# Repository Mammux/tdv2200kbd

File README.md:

# tdv2200kbd

Using the keyboard from a Tandberg **TDV 2200 S** terminal (sold by Norsk Data
as the **ND 320**, item no. 4580) as a USB keyboard on a modern computer.

<p align="center">
  
  <br>
  <sub>A TDV 2200/9S terminal sold as the ND 246 (1984), with the same family of
  NOTIS keyboard. Photo: Torfinn Ingolfsen,
  <a href="https://creativecommons.org/licenses/by-sa/3.0/">CC BY-SA 3.0</a>,
  via <a href="https://deskthority.net/wiki/File:ND246-Notis-TDV2200-9S-1984.jpg">Deskthority</a>.</sub>
</p>

The keyboard has its own 8035 microcontroller and talks to the terminal over
an RS-422 serial link. This project has two parts:

1. **An adapter**: a Raspberry Pi Pico (RP2040) and a MAX3490 RS-422
   transceiver between the keyboard's DE-9 plug and USB.
2. **New keyboard firmware**: the original firmware only sends a character
   when a key is pressed, with Shift and Ctrl applied inside the keyboard.
   A USB keyboard needs separate press and release events for every key,
   including the modifiers, so the 2716 EPROM is replaced with firmware
   that sends raw scan codes.

## Status

| Part | State |
|---|---|
| Keyboard pinout | Traced on the real keyboard, matches a 2013 cable table |
| Adapter (breadboard) | Built and working with the keyboard. The 500 mA polyfuse is left out: it dropped the keyboard's supply too far (see `docs/hardware.md`) |
| Adapter PCB (KiCad) | Schematic done, parts placed, not routed |
| Sniffer firmware (CircuitPython) | Works on the Pico with the keyboard |
| Patched original ROM (raw mode on command) | Passes all emulator tests, not tried on hardware |
| Raw-only ROM | Works on the real keyboard (in an AT28C16): correct press/release codes, `20` resets and reports `00 60`. The new version with optional 4800 baud and eager presses (about 6 ms instead of 15 ms from key to host) passes all emulator tests, not tried on hardware |
| USB keyboard firmware (CircuitPython) | **Works**: the keyboard types on a Mac through the Pico, with the raw-only ROM |
| Rust firmware (Embassy) | Milestone 1, a USB serial sniffer: builds, not yet tried on the Pico |

## Layout

| Path | Contents |
|---|---|
| [`docs/hardware.md`](docs/hardware.md) | Keyboard connector pinout, chips, memory and EEPROM replacements |
| [`docs/protocol.md`](docs/protocol.md) | Serial protocol: original and raw mode |
| [`docs/rust-plan.md`](docs/rust-plan.md) | Plan for the Rust adapter firmware and the `tdv` configuration tool |
| [`adapter/rust/`](adapter/rust/) | Rust (Embassy) adapter firmware, work in progress |
| [`docs/schematic-391170.pdf`](docs/schematic-391170.pdf) | Tandberg keyboard schematic, part no. 391170 (scan by Torfinn Ingolfsen) |
| [`adapter/build-sheet.html`](adapter/build-sheet.html) | Adapter schematic, wiring, parts list and bring-up steps (open in a browser) |
| [`adapter/code.py`](adapter/code.py) | CircuitPython sniffer: prints what the keyboard sends, sends hex bytes to it |
| [`adapter/loopback_test.py`](adapter/loopback_test.py) | Tests the Pico–MAX3490–DE-9 wiring without the keyboard |
| [`adapter/usb/`](adapter/usb/) | USB keyboard firmware for the Pico (CircuitPython) ([README](adapter/usb/README.md)) |
| [`pcb/`](pcb/) | KiCad project for the adapter board ([README](pcb/README.md)) |
| [`firmware/`](firmware/) | Keyboard ROM images, sources, 8035 emulator and tests ([README](firmware/README.md)) |

## Quick start

1. Build the adapter from `adapter/build-sheet.html`.
2. Program `firmware/965313-0-rawmode.bin` into an AT28C16 (or see
   `docs/hardware.md` for AT28C64/AT28C256), put it in socket U8 in place of the
   original 2716, and keep the original.
3. To check it, install CircuitPython on the Pico, copy `adapter/code.py` (the
   sniffer) to it and open the serial console. Each key press shows `k`, each
   release `k + 80` (`firmware/keymap.csv` lists `k` for every key). With the
   patched ROM, type `31` and Enter first to turn on raw mode.
4. To use it as a keyboard, install the USB firmware from `adapter/usb/`
   (see its README) and set the computer's layout to Norwegian.

## Rebuilding the firmware

```
cd firmware
./build_all.sh
```

This needs only Python 3. It rebuilds both ROM images from source, regenerates
the patched disassembly, and runs the emulator tests.

## Credits

* `firmware/965313-0.asm` (the disassembly of the original ROM) and the ROM dump
  are by Frode; the dump is also in the Supermagnum/Tandberg repository on GitHub.
* `docs/schematic-391170.pdf` was scanned by Torfinn Ingolfsen (2013).
* The photo at the top is by Torfinn Ingolfsen, licensed
  [CC BY-SA 3.0](https://creativecommons.org/licenses/by-sa/3.0/), and is shown
  from [Deskthority](https://deskthority.net/wiki/File:ND246-Notis-TDV2200-9S-1984.jpg)
  (it isn't stored in this repository).
* Protocol details from the Deskthority TDV 2200 S thread and NDWiki.

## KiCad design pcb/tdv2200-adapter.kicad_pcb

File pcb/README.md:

# Adapter PCB (KiCad)

KiCad project for the adapter board: Raspberry Pi Pico, MAX3490, decoupling
capacitor, a wire link where a fuse could go (F1), and the DE-9 for the keyboard.

Open `tdv2200-adapter.kicad_pro` in KiCad 7 or newer. KiCad 8/9 will offer to
upgrade the files; that's fine.

| File | What it is |
|---|---|
| `tdv2200-adapter.kicad_sch` | Schematic, same circuit as `../adapter/build-sheet.html` |
| `tdv2200-adapter.kicad_pcb` | Starting board: parts placed, nets assigned, **not routed** |
| `tdv2200.kicad_sym`, `tdv2200.pretty/` | Project symbols and footprints (Pico, MAX3490, 60R polyfuse) |
| `sym-lib-table`, `fp-lib-table` | Point KiCad at the project libraries |
| `tools/` | Scripts that generated all of the above |

## Parts and footprints

| Ref | Part | Footprint |
|---|---|---|
| U1 | Raspberry Pi Pico | `tdv2200:RaspberryPi_Pico_TH` (2 × 20 holes, 17.78 mm apart: solder the Pico on, or use 1×20 header sockets) |
| U2 | MAX3490 (DIP-8) | `Package_DIP:DIP-8_W7.62mm` |
| C1 | 100 nF ceramic, 5 mm pitch (Vishay K104K15X7RF5TL2) | `Capacitor_THT:C_Disc_D5.0mm_W2.5mm_P5.00mm` |
| F1 | **Wire link** (see below) | `tdv2200:Fuse_Littelfuse_60R_P5.10mm` (5.1 mm pitch; a wire link fits) |
| J1 | DE-9 female, right-angle | `Connector_Dsub:DSUB-9_Female_Horizontal_P2.77x2.84mm_EdgePinOffset9.90mm_Housed_MountingHolesOffset11.32mm` |
| H1-H4 | M3 mounting holes | `MountingHole:MountingHole_3.2mm_M3` |

Before ordering, check:

* **J1 gender and footprint.** The board needs the opposite gender to the
  keyboard's plug (female if the plug has pins). Right-angle DE-9s differ in
  how far the pins sit from the board edge, so pick the footprint that
  matches the connector you buy. With the one chosen here, the connector's
  flange lines up with the board's right edge.
* **F1 is a wire link.** On the real keyboard a 500 mA polyfuse (60R050XPR)
  dropped the keyboard's supply to 4.25 V, below the 4.65 V at which its
  reset chip holds the CPU, so it only beeped. With a wire link it gets
  4.93 V. If you want a fuse anyway, use one with a hold current of 1.1 A or
  more (lower resistance), and check that the keyboard still gets at least
  4.75 V. Check its lead spacing against the footprint (5.1 mm).

## Nets

| Net | Connects |
|---|---|
| KBD_RX | Pico GP1 (UART0 RX) — U2 RO |
| KBD_TX | Pico GP4 (UART1 TX) — U2 DI |
| +3V3 | Pico 3V3_OUT — U2 VCC — C1 |
| VBUS | Pico VBUS — F1 |
| KBD_5V | F1 — J1 pin 3 |
| TRANS+ / TRANS− | U2 A / B — J1 pins 9 / 4 (keyboard → host) |
| REC+ / REC− | U2 Y / Z — J1 pins 7 / 2 (host → keyboard) |
| GND | Pico GND pins — U2 GND — C1 — J1 pin 6 and shell |

## Routing tips

* Put a ground pour on the bottom layer (and optionally the top) connected to GND.
* Keep C1's tracks to U2 pins 1 and 4 as short as possible.
* 0.3–0.5 mm is plenty for the signal tracks. Use about 0.8 mm for VBUS and KBD_5V.
* Route TRANS+/TRANS− side by side, and REC+/REC− side by side.
* Run the DRC before ordering. On the unrouted board the only warnings are the
  22 unconnected pads, and silkscreen over the board edge from the DE-9 and
  the Pico's USB end (both meant to overhang).

## Regenerating

`tools/make_kicad.py` writes the schematic, libraries and project files.
`tools/make_board.py` builds the starting board from the schematic's netlist.
They need KiCad's standard libraries in `/usr/share/kicad` and, for the board,
KiCad's Python module (`pcbnew`):

```
python3 tools/make_kicad.py
kicad-cli sch export netlist -o /tmp/adapter.net tdv2200-adapter.kicad_sch
python3 tools/make_board.py /tmp/adapter.net
```

Once you start editing in KiCad, edit there and don't regenerate: the scripts
overwrite the files.

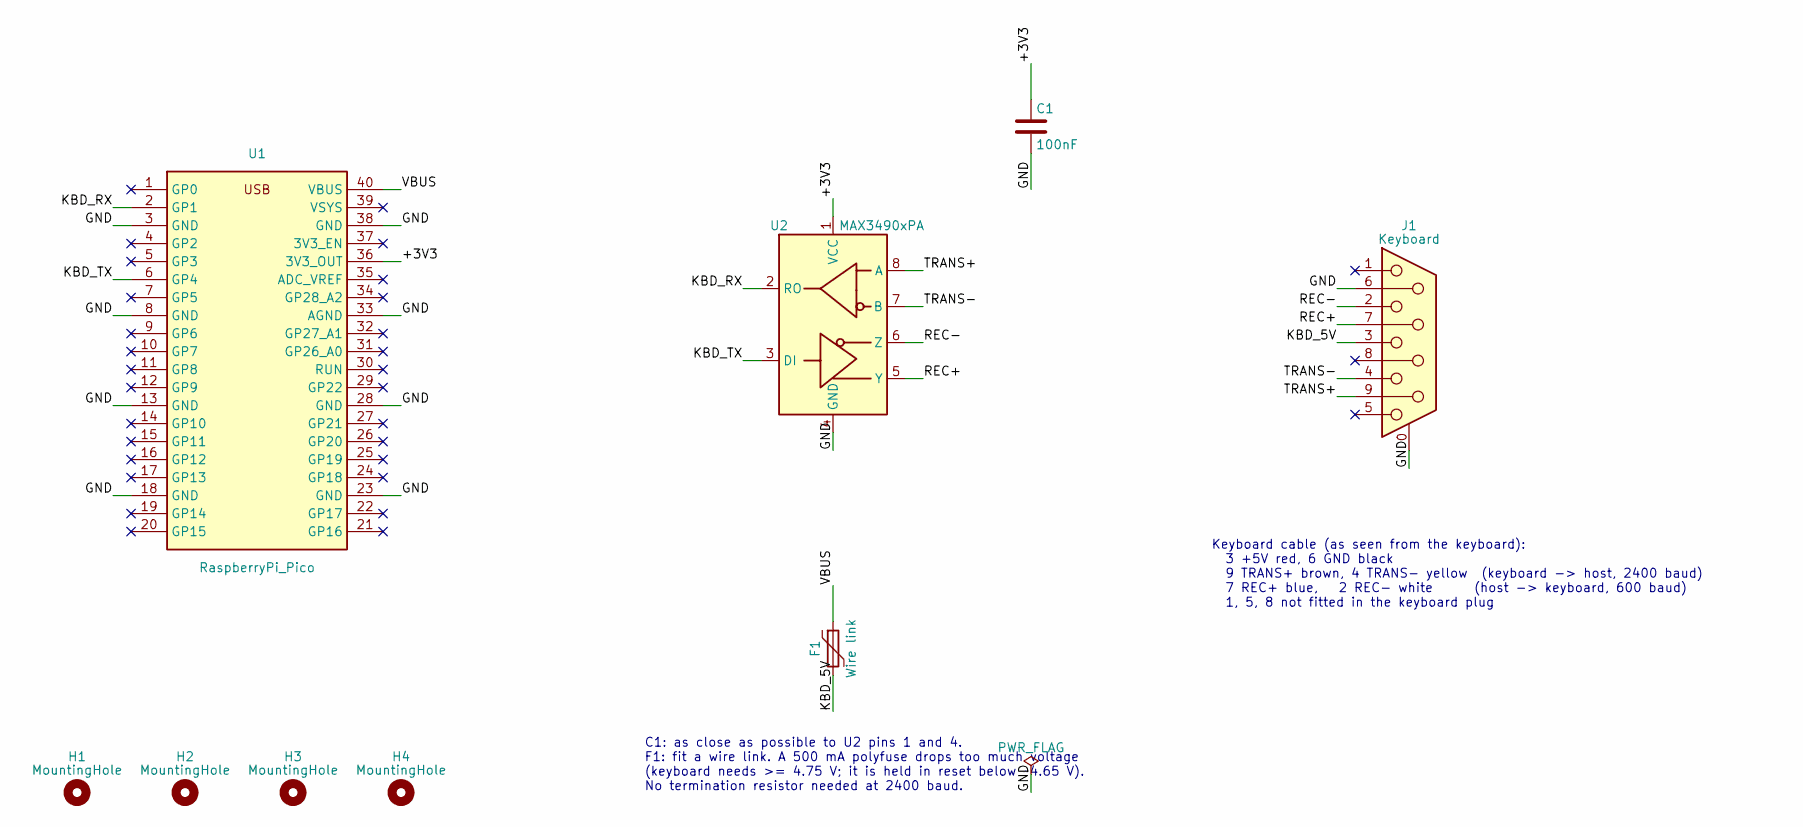
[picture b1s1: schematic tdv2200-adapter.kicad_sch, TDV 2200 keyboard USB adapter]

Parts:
C1: 100nF; C_Disc_D5.0mm_W2.5mm_P5.00mm; MPN Vishay K104K15X7RF5TL2
F1: Wire link; Fuse_Littelfuse_60R_P5.10mm
H1, H2, H3, H4: MountingHole; MountingHole_3.2mm_M3
J1: Keyboard; DSUB-9_Female_Horizontal_P2.77x2.84mm_EdgePinOffset9.90mm_H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
U1: RaspberryPi_Pico; RaspberryPi_Pico_TH
U2: MAX3490xPA; DIP-8_W7.62mm

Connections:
+3V3: C1.1, U1.36 (3V3_OUT), U2.1 (VCC)
GND: C1.2, J1.0 (PAD), J1.6, U1.3 (GND), U1.8 (GND), U1.13 (GND), U1.18 (GND), U1.23 (GND), U1.28 (GND), U1.33 (AGND), U1.38 (GND), U2.4 (GND)
KBD_5V: F1.2, J1.3
KBD_RX: U1.2 (GP1), U2.2 (RO)
KBD_TX: U1.6 (GP4), U2.3 (DI)
REC+: J1.7, U2.5 (Y)
REC-: J1.2, U2.6 (Z)
TRANS+: J1.9, U2.8 (A)
TRANS-: J1.4, U2.7 (B)
VBUS: F1.1, U1.40 (VBUS)

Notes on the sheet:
Keyboard cable (as seen from the keyboard): 3 +5V red, 6 GND black 9 TRANS+ brown, 4 TRANS- yellow (keyboard -> host, 2400 baud) 7 REC+ blue, 2 REC- white (host -> keyboard, 600 baud) 1, 5, 8 not fitted in the keyboard plug
C1: as close as possible to U2 pins 1 and 4. F1: fit a wire link. A 500 mA polyfuse drops too much voltage (keyboard needs >= 4.75 V; it is held in reset below ~4.65 V). No termination resistor needed at 2400 baud.

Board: 2 copper layers, 9 parts (0 on the bottom side), 10 nets, no tracks yet.

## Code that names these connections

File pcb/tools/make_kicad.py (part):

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    for n, name in PICO_PINS.items():
        if name in ("GND", "AGND"):
            sh.label("U1", str(n), "GND")
    sh.label("U1", "2", "KBD_RX")          # GP1, UART0 RX, 2400 baud from keyboard
    sh.label("U1", "6", "KBD_TX")          # GP4, UART1 TX, 600 baud to keyboard
    sh.label("U1", "36", "+3V3")
    sh.label("U1", "40", "VBUS")
    for n in PICO_PINS:
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    # MAX3490
    sh.label("U2", "1", "+3V3")
    sh.label("U2", "4", "GND")
    sh.label("U2", "2", "KBD_RX")
    sh.label("U2", "3", "KBD_TX")
    sh.label("U2", "8", "TRANS+")
    sh.label("U2", "7", "TRANS-")
    sh.label("U2", "5", "REC+")
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
    # power to the keyboard
    sh.label("F1", "1", "VBUS", 5.08)
    sh.label("F1", "2", "KBD_5V", 5.08)
    sh.label("#FLG01", "1", "GND")

    # keyboard connector
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    sh.label("J1", "4", "TRANS-")
    sh.label("J1", "7", "REC+")
    sh.label("J1", "2", "REC-")
    sh.label("J1", "3", "KBD_5V")
    sh.label("J1", "6", "GND")
    sh.label("J1", "0", "GND")
    for n in ("1", "5", "8"):
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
